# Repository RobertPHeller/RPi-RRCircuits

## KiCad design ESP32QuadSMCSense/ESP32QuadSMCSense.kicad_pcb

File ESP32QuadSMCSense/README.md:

# ESP32QuadSMCSense

ESP32 Quad Stall Motor w/ sense node.

* [Order this board from The Country Robot](https://www.thecountryrobot.com/product/quad-stall-motor-control-and-sense-board-for-esp32-bare-circuit-board-w-doc/)
* [Order this board from PCBWay](https://www.pcbway.com/project/shareproject/ESP32QuadSMCSense.html)

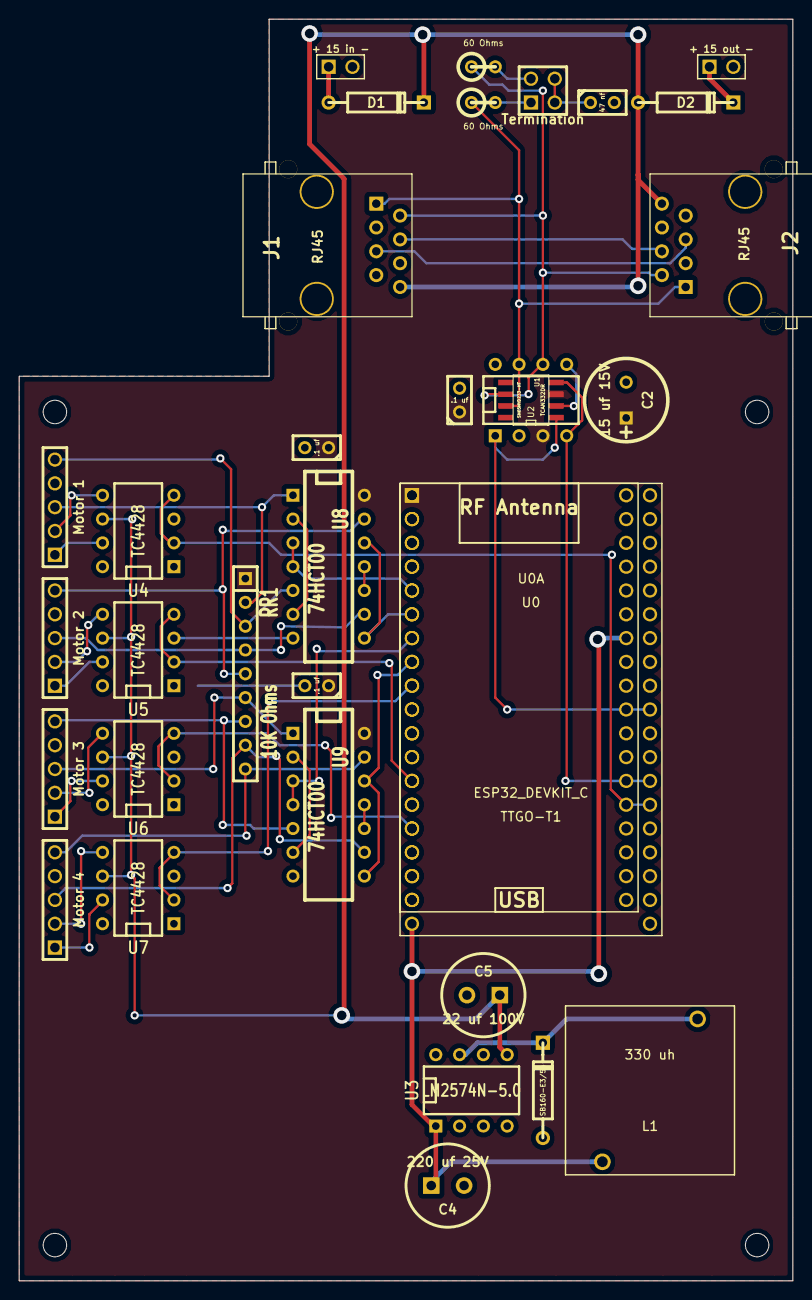
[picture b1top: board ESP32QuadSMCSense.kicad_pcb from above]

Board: 2 copper layers, 82.5 x 134.6 mm, 38 parts (0 on the bottom side), 44 nets.

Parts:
C1, C6, C7: .1 uf; C1
C2: 15 uf 15V; C1.5V8V
C3: 47 nf; C1
C4: 220 uf 25V; C1-3V8
C5: 22 uf 100V; C1-3V8
D1, D2: SB240E; DO-41
D3: SB160-E3/54; DO-41
J1, J2: RJ45; RJ45_8N-S
JP1: Termination; PIN_ARRAY_2X2
L1: 330 uh; PE-LowProfile
MH: MountingHole_2-5mm_RevA_Date21Jun2010
MH#2, MH#3, MH#4: MountingHole_2-5mm_RevA_Date21Jun2010
R1, R2: 60 Ohms; R1
RR1: 10K Ohms; SIL-9
T1: + 15 in -; ScrewTerm2.54-2
T2: + 15 out -; ScrewTerm2.54-2
T3: Motor 1; ScrewTerm_2.54-5
T4: Motor 2; ScrewTerm_2.54-5
T5: Motor 3; ScrewTerm_2.54-5
T6: Motor 4; ScrewTerm_2.54-5
U0: ESP32_DEVKIT_C; ESP32-Devkit-C
U0A: TTGO-T1; TIGO-T1
U1: TCAN332DR; SOIC-8_N
U2: SN65HVD233-HT; DIP-8__300
U3: LM2574N-5.0; DIP-8__300
U4, U5, U6, U7: TC4428; DIP-8__300
U8, U9: 74HCT00; DIP-14__300

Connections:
3V3: C1.1, C2.1, C6.1, C7.1, RR1.1, U0.1, U0A.1, U1.3, U2.3, U8.14, U9.14
+5V: C4.1, L1.1, U0.19, U0A.30, U3.1
+12V: C5.1, D1.2, D2.1, J1.8, J2.8, U3.5, U4.6, U5.6, U6.6, U7.6
/CAN Transceiver/CANH: J1.1, J2.1, R1.1, U1.7, U2.7
/CAN Transceiver/CANL: J1.2, J2.2, R2.1, U1.6, U2.6
/CAN Transceiver/CAN_RX: U0.26, U0A.24, U1.4, U2.4
/CAN Transceiver/CAN_TX: U0.29, U0A.27, U1.1, U2.1
/Motor1A: T3.1, U4.7
/Motor1B: T3.2, U4.5
/Motor2A: T4.1, U5.7
/Motor2B: T4.2, U5.5
/Motor3A: T5.1, U6.7
/Motor3B: T5.2, U6.5
/Motor4A: T6.1, U7.7
/Motor4B: T6.2, U7.5
/Motor 1: U0.25, U0A.23, U4.2, U4.4
/Motor 2: U0.13, U0A.13, U5.2, U5.4
/Motor 3: U0.15, U0A.15, U6.2, U6.4
/Motor 4: U0.9, U0A.9, U7.2, U7.4
/Points 1A: RR1.2, T3.3, U8.1
/Points 1B: RR1.3, T3.5, U8.5
/Points 2A: RR1.4, T4.3, U8.9
/Points 2B: RR1.5, T4.5, U8.13
/Points 3A: RR1.6, T5.3, U9.1
/Points 3B: RR1.7, T5.5, U9.5
/Points 4A: RR1.8, T6.3, U9.9
/Points 4B: RR1.9, T6.5, U9.13
/Sense 1: U0.5, U0A.5, U8.3, U8.4
/Sense 2: U0.6, U0A.6, U8.8, U8.12
/Sense 3: U0.7, U0A.7, U9.3, U9.4
/Sense 4: U0.8, U0A.8, U9.8, U9.12
GND: C1.2, C2.2, C3.2, C4.2, C5.2, C6.2, C7.2, D3.1, J1.3, J1.6, J1.7, J2.3, J2.6, J2.7, T1.2, T2.2, T3.4, T4.4, T5.4, T6.4, U0.14, U0.32, U0.38, U0A.14, U0A.36, U1.2, U2.2, U2.5, U2.8, U3.2, U3.3, U3.4, U4.3, U5.3, U6.3, U7.3, U8.7, U9.7
unnamed: U9.10, U9.11
unnamed: U8.10, U8.11
unnamed: U8.2, U8.6
unnamed: U9.2, U9.6
unnamed: J1.4, J2.4
unnamed: J1.5, J2.5
unnamed: D1.1, T1.1
unnamed: D2.2, T2.1
unnamed: JP1.2, R2.2
unnamed: JP1.1, R1.2
unnamed: C3.1, JP1.3, JP1.4
unnamed: D3.2, L1.2, U3.7

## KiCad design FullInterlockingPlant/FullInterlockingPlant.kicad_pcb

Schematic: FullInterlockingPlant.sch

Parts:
J1: RPI_GPIO
P1, P2, P3: CONN_5

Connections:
#4: J1.7, P1.2
#5: J1.29, P2.1
#6: J1.31, P2.2
#12: J1.32, P2.3
#13: J1.33, P2.4
#16: J1.36, P2.5
#19: J1.35, P3.1
#20: J1.38, P3.2
#21: J1.40, P3.3
#23: J1.16, P1.3
#24: J1.18, P1.4
#25: J1.22, P1.5
#26: J1.37, P3.4
+3.3V: J1.1, J1.17, P1.1; also elsewhere on the board
+5V: J1.2, J1.4; also elsewhere on the board
/StallMotors/M Select 2: J1.12; also elsewhere on the board
/StallMotors/MSelect 1: J1.11; also elsewhere on the board
/StallMotors/Point Sense 1: J1.13; also elsewhere on the board
/StallMotors/Point Sense 2: J1.15; also elsewhere on the board
GND: J1.6, J1.9, J1.14, J1.20, J1.25, J1.30, J1.34, J1.39, P3.5; also elsewhere on the board
SCL: J1.5; also elsewhere on the board
SDA: J1.3; also elsewhere on the board

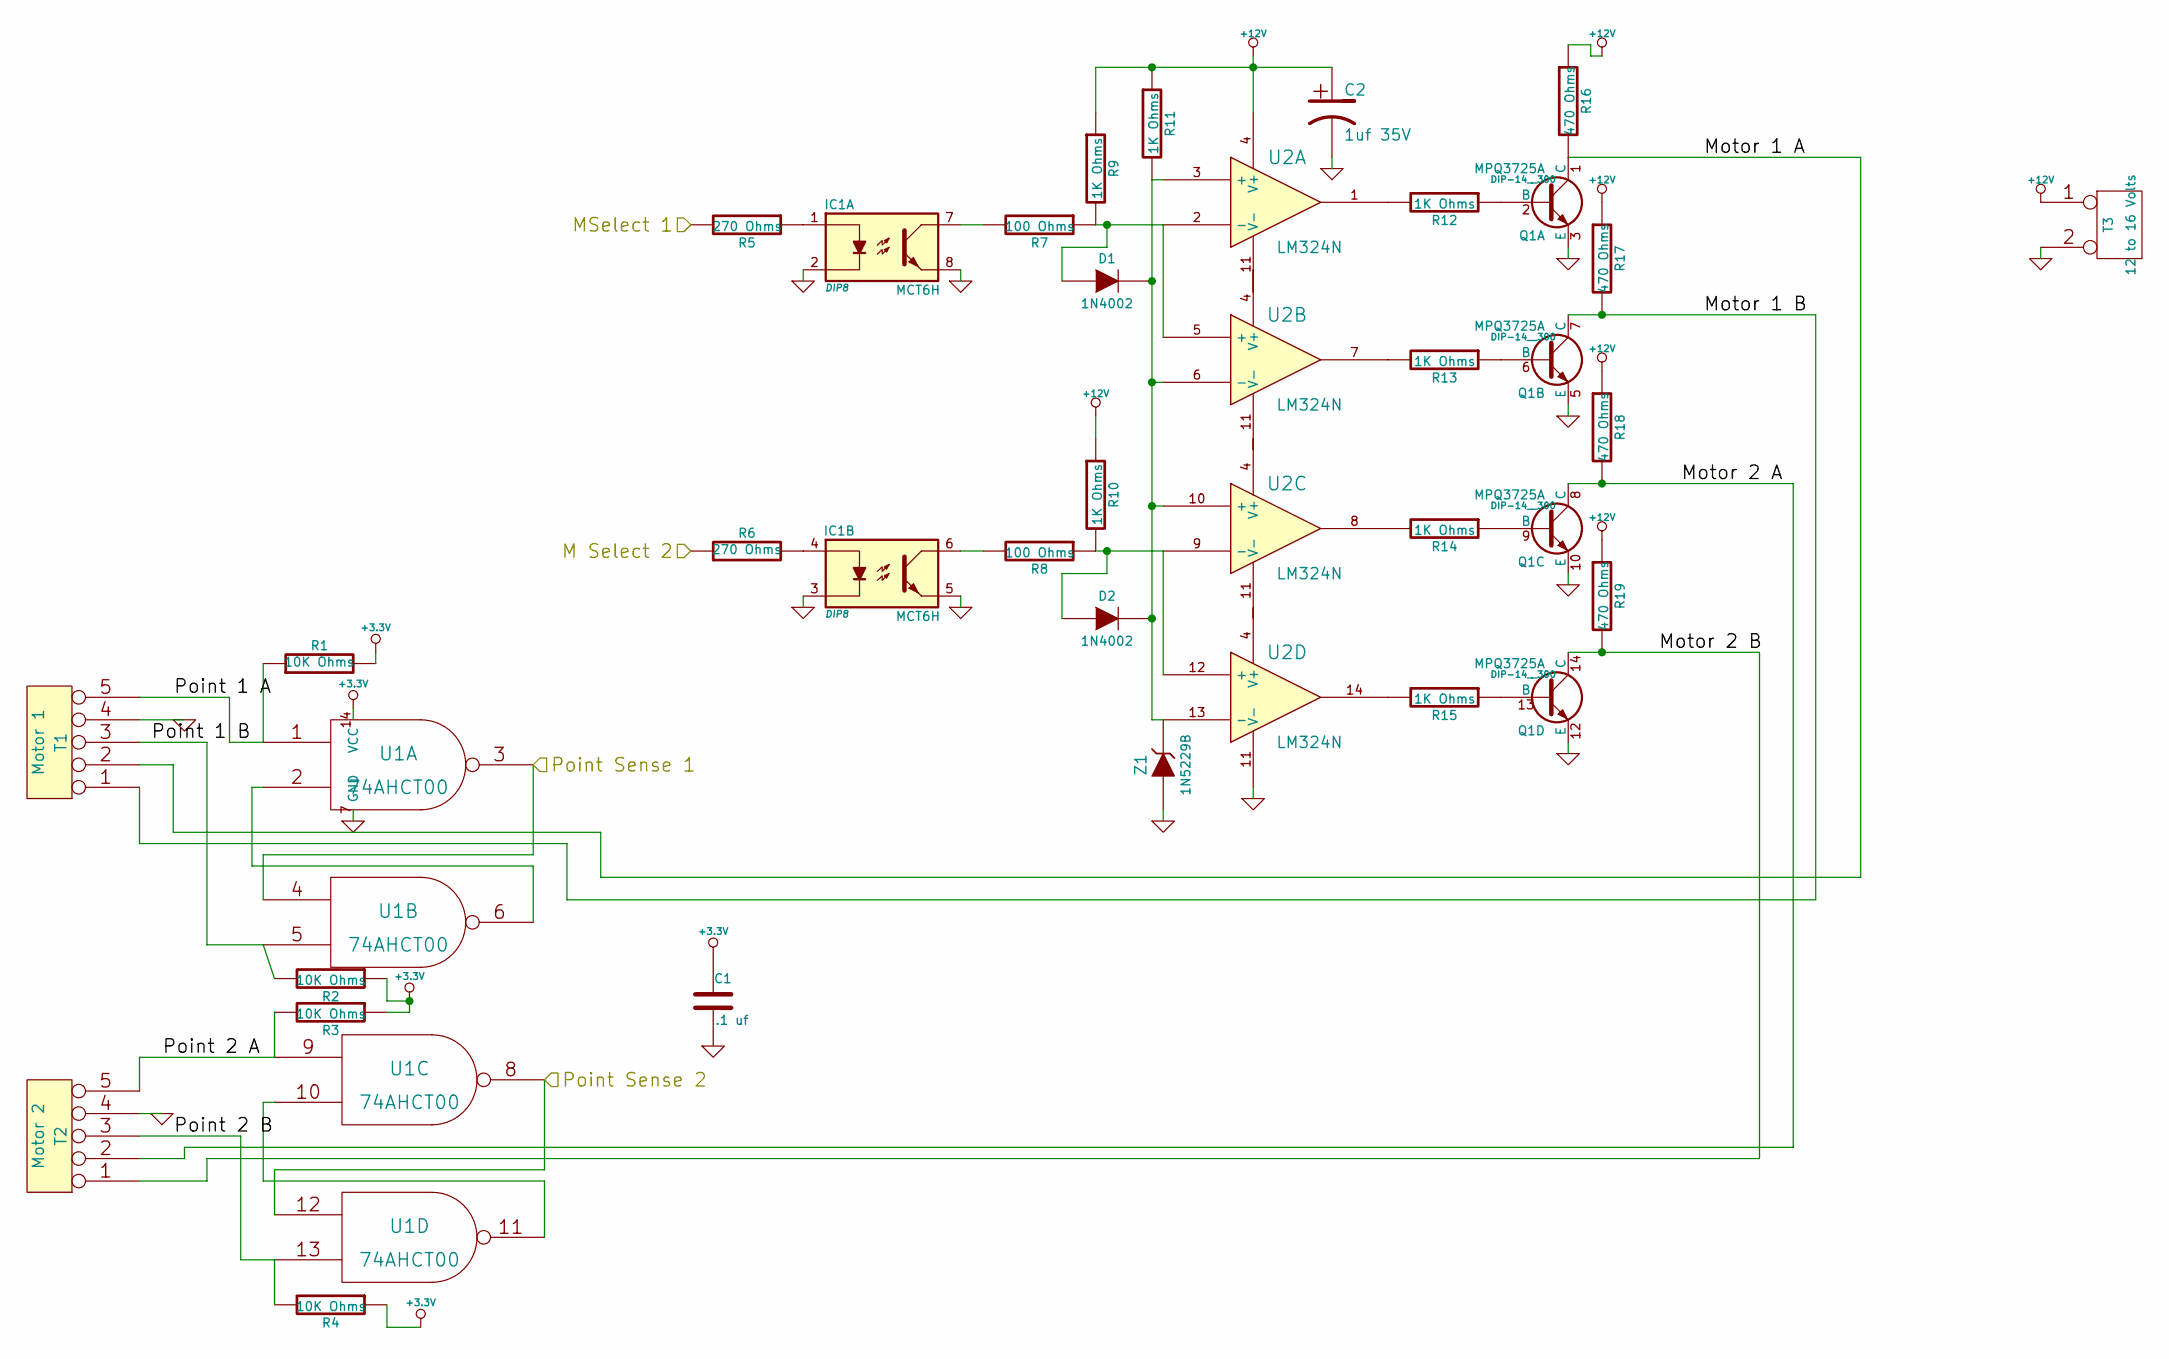
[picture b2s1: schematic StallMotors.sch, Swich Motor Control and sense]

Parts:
C1: .1 uf; Mouser part Number 21RZ310-RC
C2: 1uf 35V; Mouser Part Number 74-199D105X9035A1VE3
D1, D2: 1N4002; Mouser Part Number 833-1N4002-TP
IC1: MCT6H; DIP8; Mouser part Number 782-MCT6H
Q1: MPQ3725A; DIP-14__300; Mouser part Number 610-MPQ3725A
R1, R2, R3, R4: 10K Ohms; Mouser Part Number 603-CFR-25JR-5210K
R5, R6: 270 Ohms; Mouser Part Number 603-CFR-25JR-52-270R
R7, R8: 100 Ohms; Mouser Part Number 603-CFR-25JR-52100R
R9: 1K Ohms; Mouser part Number 279-2-1623927-3
R10, R11, R12, R13, R14, R15: 1K Ohms; Mouser Part Number 279-2-1623927-3
R16: 470 Ohms; Mouser part Number 279-CFR50J470R
R17, R18: 470 Ohms; Mouser Part Number 279-CFR50J470R
R19: 470 Ohms; Mousere Part Number 279-CFR50J470R
T1: Motor 1; Mouser Part Number 571-282834-5
T2: Motor 2; Mouser Part Number 571-282834-5
T3: 12 to 16 Volts; Mouser Partnumber 571-282834-2
U1: 74AHCT00; Mouser part Number 595-SN74AHC00N
U2: LM324N; Mouser part Number 512-LM324N
Z1: 1N5229B; Mouser Part Number 512-1N5229BTR

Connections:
+3.3V: C1.1, R1.2, R2.1, R3.1, R4.1, U1.14 (VCC); also elsewhere on the board
+12V: C2.1, R9.1, R10.1, R11.1, R16.1, R17.1, R18.1, R19.1, T3.1, U2.4 (V+)
/StallMotors/M Select 2: R6.1; also elsewhere on the board
/StallMotors/MSelect 1: R5.2; also elsewhere on the board
/StallMotors/Motor 1 A: Q1.1 (C), R16.2, T1.2
/StallMotors/Motor 1 B: Q1.7 (C), R17.2, T1.1
/StallMotors/Motor 2 A: Q1.8 (C), R18.2, T2.2
/StallMotors/Motor 2 B: Q1.14 (C), R19.2, T2.1
/StallMotors/Point 1 A: R1.1, T1.5, U1.1
/StallMotors/Point 1 B: R2.2, T1.3, U1.5
/StallMotors/Point 2 A: R3.2, T2.5, U1.9
/StallMotors/Point 2 B: R4.2, T2.3, U1.13
/StallMotors/Point Sense 1: U1.3, U1.4; also elsewhere on the board
/StallMotors/Point Sense 2: U1.8, U1.12; also elsewhere on the board
GND: C1.2, C2.2, IC1.2, IC1.3, IC1.5, IC1.8, Q1.3 (E), Q1.5 (E), Q1.10 (E), Q1.12 (E), T1.4, T2.4, T3.2 (PM), U1.7 (GND), U2.11 (V-), Z1.1 (A); also elsewhere on the board
unnamed: Q1.6 (B), R13.1
unnamed: Q1.9 (B), R14.1
unnamed: Q1.13 (B), R15.1
unnamed: Q1.2 (B), R12.1
unnamed: R12.2, U2.1
unnamed: R13.2, U2.7
unnamed: R14.2, U2.8
unnamed: R15.2, U2.14
unnamed: IC1.6, R8.2
unnamed: D2.1 (A), R8.1, R10.2, U2.9 (-), U2.12 (+)
unnamed: IC1.4, R6.2
unnamed: IC1.1, R5.1
unnamed: U1.2, U1.6
unnamed: IC1.7, R7.2
unnamed: U1.10, U1.11
unnamed: D1.2 (K), D2.2 (K), R11.2, U2.3 (+), U2.6 (-), U2.10 (+), U2.13 (-), Z1.2 (K)
unnamed: D1.1 (A), R7.1, R9.2, U2.2 (-), U2.5 (+)

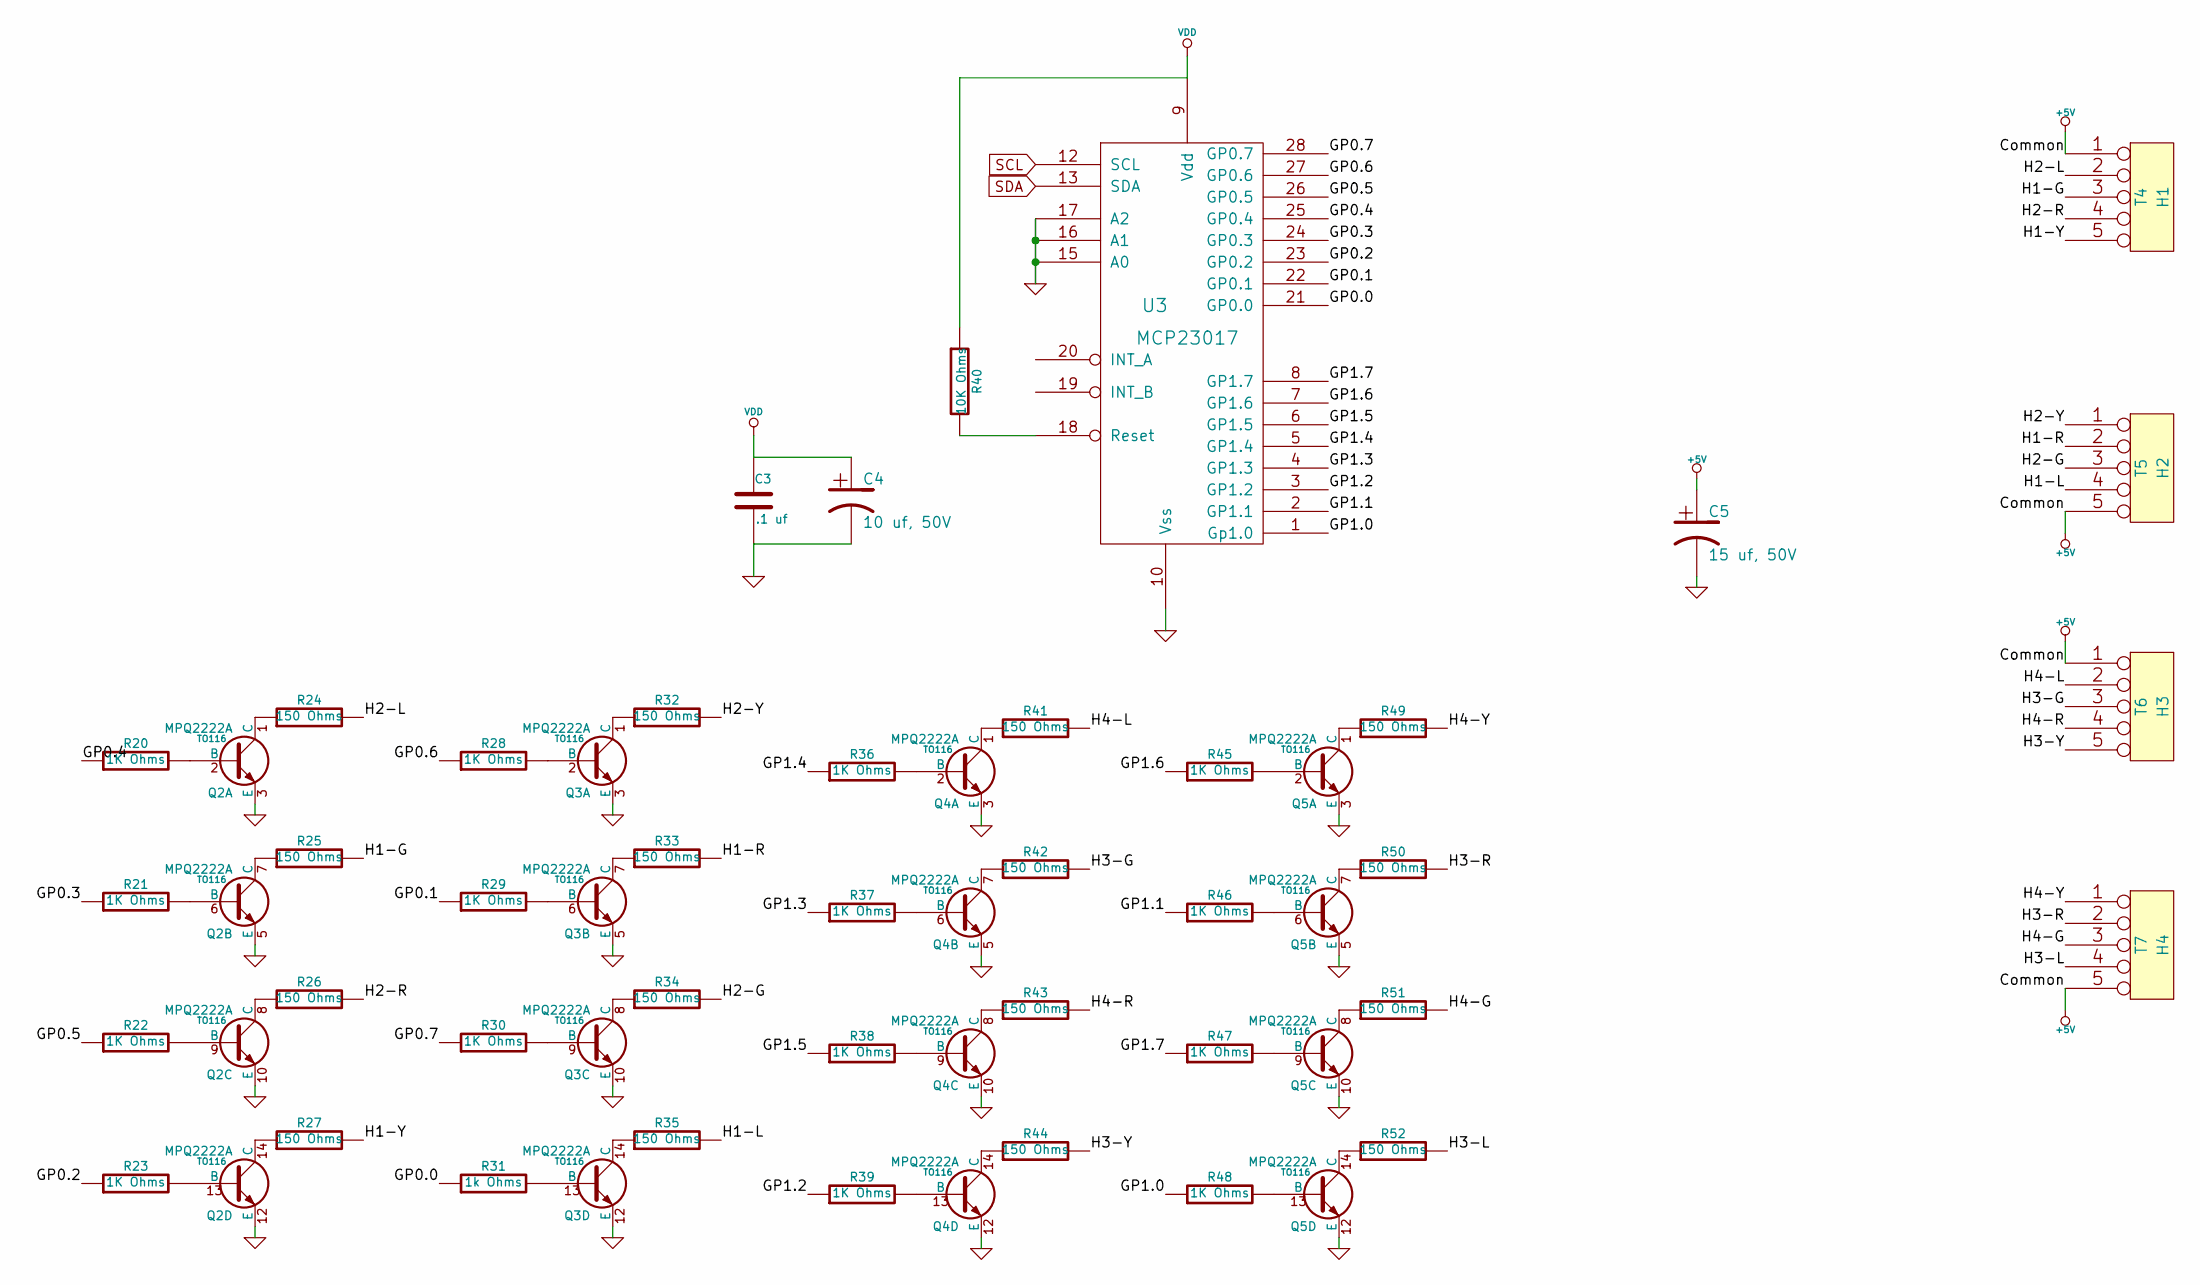
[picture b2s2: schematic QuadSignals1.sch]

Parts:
C3: .1 uf
C4: 10 uf, 50V
C5: 15 uf, 50V
Q2, Q3, Q4, Q5: MPQ2222A; TO116
R20, R21, R22, R23, R28, R29, R30, R36, R37, R38, R39, R45, R46, R47, R48: 1K Ohms
R24, R25, R26, R27, R32, R33, R34, R35, R41, R42, R43, R44, R49, R50, R51, R52: 150 Ohms
R31: 1k Ohms
R40: 10K Ohms
T4: H1
T5: H2
T6: H3
T7: H4
U3: MCP23017

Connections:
+3.3V: C3.1, C4.1, R40.1, U3.9 (Vdd); also elsewhere on the board
+5V: C5.1, T4.1, T5.5, T6.1, T7.5; also elsewhere on the board
/Quad Signals 1/GP0.0: R31.1, U3.21 (GP0.0)
/Quad Signals 1/GP0.1: R29.1, U3.22 (GP0.1)
/Quad Signals 1/GP0.2: R23.1, U3.23 (GP0.2)
/Quad Signals 1/GP0.3: R21.1, U3.24 (GP0.3)
/Quad Signals 1/GP0.4: R20.1, U3.25 (GP0.4)
/Quad Signals 1/GP0.5: R22.1, U3.26 (GP0.5)
/Quad Signals 1/GP0.6: R28.1, U3.27 (GP0.6)
/Quad Signals 1/GP0.7: R30.1, U3.28 (GP0.7)
/Quad Signals 1/GP1.0: R48.1, U3.1 (Gp1.0)
/Quad Signals 1/GP1.1: R46.1, U3.2 (GP1.1)
/Quad Signals 1/GP1.2: R39.1, U3.3 (GP1.2)
/Quad Signals 1/GP1.3: R37.1, U3.4 (GP1.3)
/Quad Signals 1/GP1.4: R36.1, U3.5 (GP1.4)
/Quad Signals 1/GP1.5: R38.1, U3.6 (GP1.5)
/Quad Signals 1/GP1.6: R45.1, U3.7 (GP1.6)
/Quad Signals 1/GP1.7: R47.1, U3.8 (GP1.7)
/Quad Signals 1/H1-G: R25.2, T4.3
/Quad Signals 1/H1-L: R35.2, T5.4
/Quad Signals 1/H1-R: R33.2, T5.2
/Quad Signals 1/H1-Y: R27.2, T4.5
/Quad Signals 1/H2-G: R34.2, T5.3
/Quad Signals 1/H2-L: R24.2, T4.2
/Quad Signals 1/H2-R: R26.2, T4.4
/Quad Signals 1/H2-Y: R32.2, T5.1
/Quad Signals 1/H3-G: R42.2, T6.3
/Quad Signals 1/H3-L: R52.2, T7.4
/Quad Signals 1/H3-R: R50.2, T7.2
/Quad Signals 1/H3-Y: R44.2, T6.5
/Quad Signals 1/H4-G: R51.2, T7.3
/Quad Signals 1/H4-L: R41.2, T6.2
/Quad Signals 1/H4-R: R43.2, T6.4
/Quad Signals 1/H4-Y: R49.2, T7.1
GND: C3.2, C4.2, C5.2, Q2.3 (E), Q2.5 (E), Q2.10 (E), Q2.12 (E), Q3.3 (E), Q3.5 (E), Q3.10 (E), Q3.12 (E), Q4.3 (E), Q4.5 (E), Q4.10 (E), Q4.12 (E), Q5.3 (E), Q5.5 (E), Q5.10 (E), Q5.12 (E), U3.10 (Vss), U3.15 (A0), U3.16 (A1), U3.17 (A2); also elsewhere on the board
unnamed: Q5.14 (C), R52.1
unnamed: Q5.13 (B), R48.2
unnamed: Q5.8 (C), R51.1
unnamed: Q5.9 (B), R47.2
unnamed: R40.2, U3.18 (Reset)
unnamed: Q2.13 (B), R23.2
unnamed: Q2.14 (C), R27.1
unnamed: Q2.8 (C), R26.1
unnamed: Q2.9 (B), R22.2
unnamed: Q2.7 (C), R25.1
unnamed: Q3.6 (B), R29.2
unnamed: Q3.7 (C), R33.1
unnamed: Q3.1 (C), R32.1
unnamed: Q3.2 (B), R28.2
unnamed: Q2.6 (B), R21.2
unnamed: Q2.1 (C), R24.1
unnamed: Q2.2 (B), R20.2
unnamed: Q4.14 (C), R44.1
unnamed: Q4.13 (B), R39.2
unnamed: Q4.8 (C), R43.1
unnamed: Q4.9 (B), R38.2
unnamed: Q5.7 (C), R50.1
unnamed: Q5.6 (B), R46.2
unnamed: Q5.1 (C), R49.1
unnamed: Q5.2 (B), R45.2
unnamed: Q3.13 (B), R31.2
unnamed: Q3.14 (C), R35.1
unnamed: Q3.8 (C), R34.1
unnamed: Q3.9 (B), R30.2
unnamed: Q4.7 (C), R42.1
unnamed: Q4.6 (B), R37.2
unnamed: Q4.1 (C), R41.1
unnamed: Q4.2 (B), R36.2
SCL: U3.12 (SCL); also elsewhere on the board
SDA: U3.13 (SDA); also elsewhere on the board

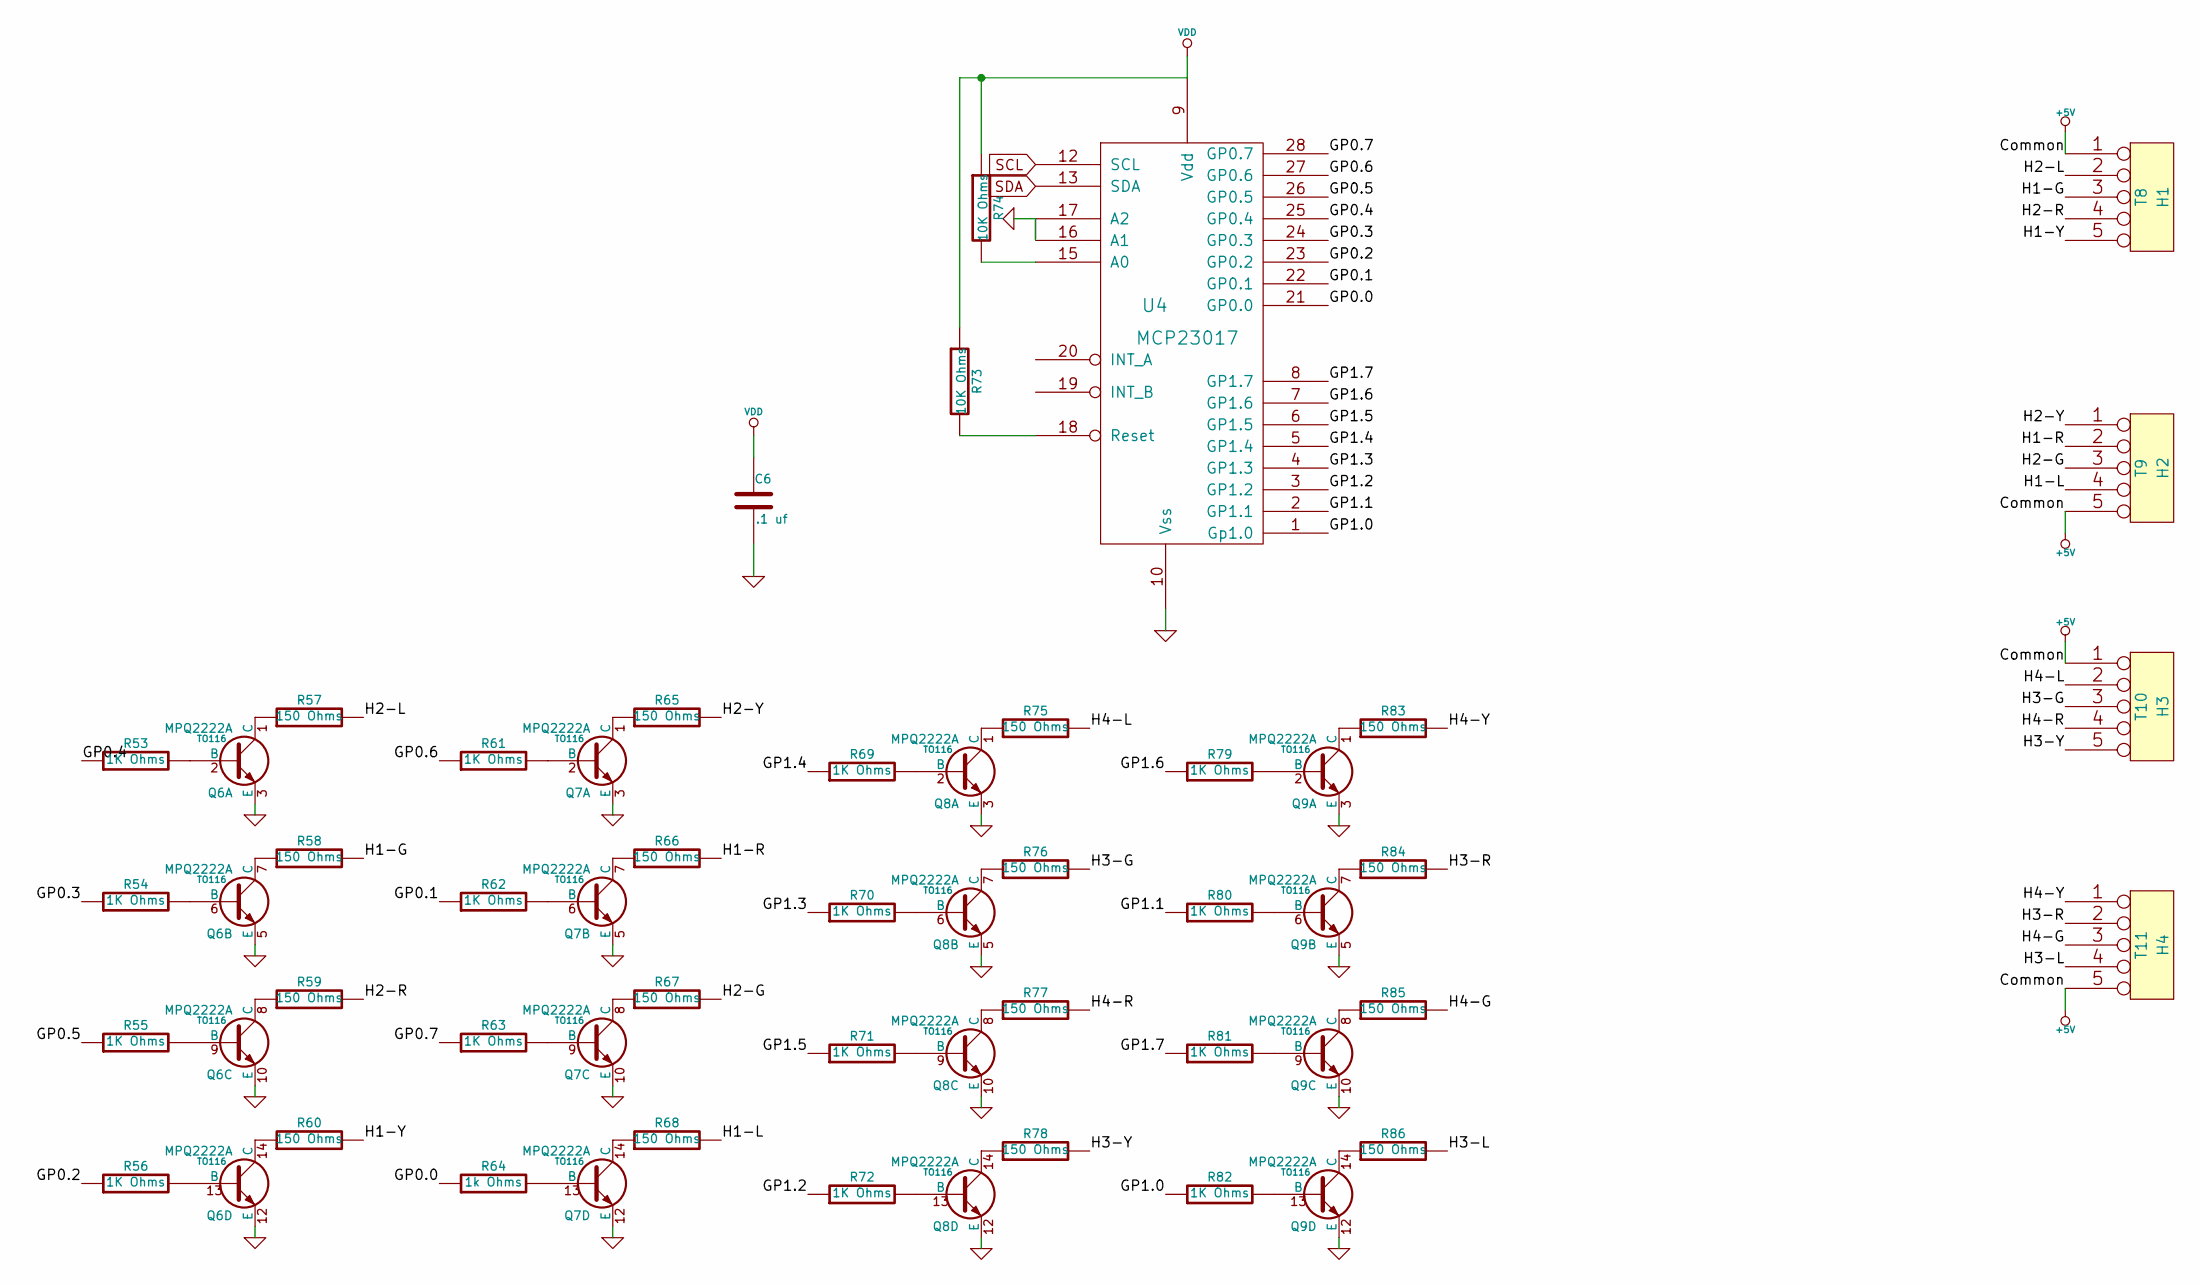
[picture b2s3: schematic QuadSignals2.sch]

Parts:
C6: .1 uf
Q6, Q7, Q8, Q9: MPQ2222A; TO116
R53, R54, R55, R56, R61, R62, R63, R69, R70, R71, R72, R79, R80, R81, R82: 1K Ohms
R57, R58, R59, R60, R65, R66, R67, R68, R75, R76, R77, R78, R83, R84, R85, R86: 150 Ohms
R64: 1k Ohms
R73, R74: 10K Ohms
T8: H1
T9: H2
T10: H3
T11: H4
U4: MCP23017

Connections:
+3.3V: C6.1, R73.1, R74.1, U4.9 (Vdd); also elsewhere on the board
+5V: T8.1, T9.5, T10.1, T11.5; also elsewhere on the board
/Quad Signals 2/GP0.0: R64.1, U4.21 (GP0.0)
/Quad Signals 2/GP0.1: R62.1, U4.22 (GP0.1)
/Quad Signals 2/GP0.2: R56.1, U4.23 (GP0.2)
/Quad Signals 2/GP0.3: R54.1, U4.24 (GP0.3)
/Quad Signals 2/GP0.4: R53.1, U4.25 (GP0.4)
/Quad Signals 2/GP0.5: R55.1, U4.26 (GP0.5)
/Quad Signals 2/GP0.6: R61.1, U4.27 (GP0.6)
/Quad Signals 2/GP0.7: R63.1, U4.28 (GP0.7)
/Quad Signals 2/GP1.0: R82.1, U4.1 (Gp1.0)
/Quad Signals 2/GP1.1: R80.1, U4.2 (GP1.1)
/Quad Signals 2/GP1.2: R72.1, U4.3 (GP1.2)
/Quad Signals 2/GP1.3: R70.1, U4.4 (GP1.3)
/Quad Signals 2/GP1.4: R69.1, U4.5 (GP1.4)
/Quad Signals 2/GP1.5: R71.1, U4.6 (GP1.5)
/Quad Signals 2/GP1.6: R79.1, U4.7 (GP1.6)
/Quad Signals 2/GP1.7: R81.1, U4.8 (GP1.7)
/Quad Signals 2/H1-G: R58.2, T8.3
/Quad Signals 2/H1-L: R68.2, T9.4
/Quad Signals 2/H1-R: R66.2, T9.2
/Quad Signals 2/H1-Y: R60.2, T8.5
/Quad Signals 2/H2-G: R67.2, T9.3
/Quad Signals 2/H2-L: R57.2, T8.2
/Quad Signals 2/H2-R: R59.2, T8.4
/Quad Signals 2/H2-Y: R65.2, T9.1
/Quad Signals 2/H3-G: R76.2, T10.3
/Quad Signals 2/H3-L: R86.2, T11.4
/Quad Signals 2/H3-R: R84.2, T11.2
/Quad Signals 2/H3-Y: R78.2, T10.5
/Quad Signals 2/H4-G: R85.2, T11.3
/Quad Signals 2/H4-L: R75.2, T10.2
/Quad Signals 2/H4-R: R77.2, T10.4
/Quad Signals 2/H4-Y: R83.2, T11.1
GND: C6.2, Q6.3 (E), Q6.5 (E), Q6.10 (E), Q6.12 (E), Q7.3 (E), Q7.5 (E), Q7.10 (E), Q7.12 (E), Q8.3 (E), Q8.5 (E), Q8.10 (E), Q8.12 (E), Q9.3 (E), Q9.5 (E), Q9.10 (E), Q9.12 (E), U4.10 (Vss), U4.16 (A1), U4.17 (A2); also elsewhere on the board
unnamed: Q9.13 (B), R82.2
unnamed: Q9.8 (C), R85.1
unnamed: Q9.9 (B), R81.2
unnamed: Q9.7 (C), R84.1
unnamed: Q9.6 (B), R80.2
unnamed: Q9.14 (C), R86.1
unnamed: R74.2, U4.15 (A0)
unnamed: R73.2, U4.18 (Reset)
unnamed: Q6.14 (C), R60.1
unnamed: Q6.13 (B), R56.2
unnamed: Q6.8 (C), R59.1
unnamed: Q6.9 (B), R55.2
unnamed: Q6.7 (C), R58.1
unnamed: Q6.6 (B), R54.2
unnamed: Q7.7 (C), R66.1
unnamed: Q7.6 (B), R62.2
unnamed: Q7.1 (C), R65.1
unnamed: Q7.2 (B), R61.2
unnamed: Q6.1 (C), R57.1
unnamed: Q6.2 (B), R53.2
unnamed: Q8.13 (B), R72.2
unnamed: Q8.8 (C), R77.1
unnamed: Q8.9 (B), R71.2
unnamed: Q8.7 (C), R76.1
unnamed: Q8.6 (B), R70.2
unnamed: Q9.1 (C), R83.1
unnamed: Q9.2 (B), R79.2
unnamed: Q8.14 (C), R78.1
unnamed: Q7.14 (C), R68.1
unnamed: Q7.13 (B), R64.2
unnamed: Q7.8 (C), R67.1
unnamed: Q7.9 (B), R63.2
unnamed: Q8.1 (C), R75.1
unnamed: Q8.2 (B), R69.2
SCL: U4.12 (SCL); also elsewhere on the board
SDA: U4.13 (SDA); also elsewhere on the board

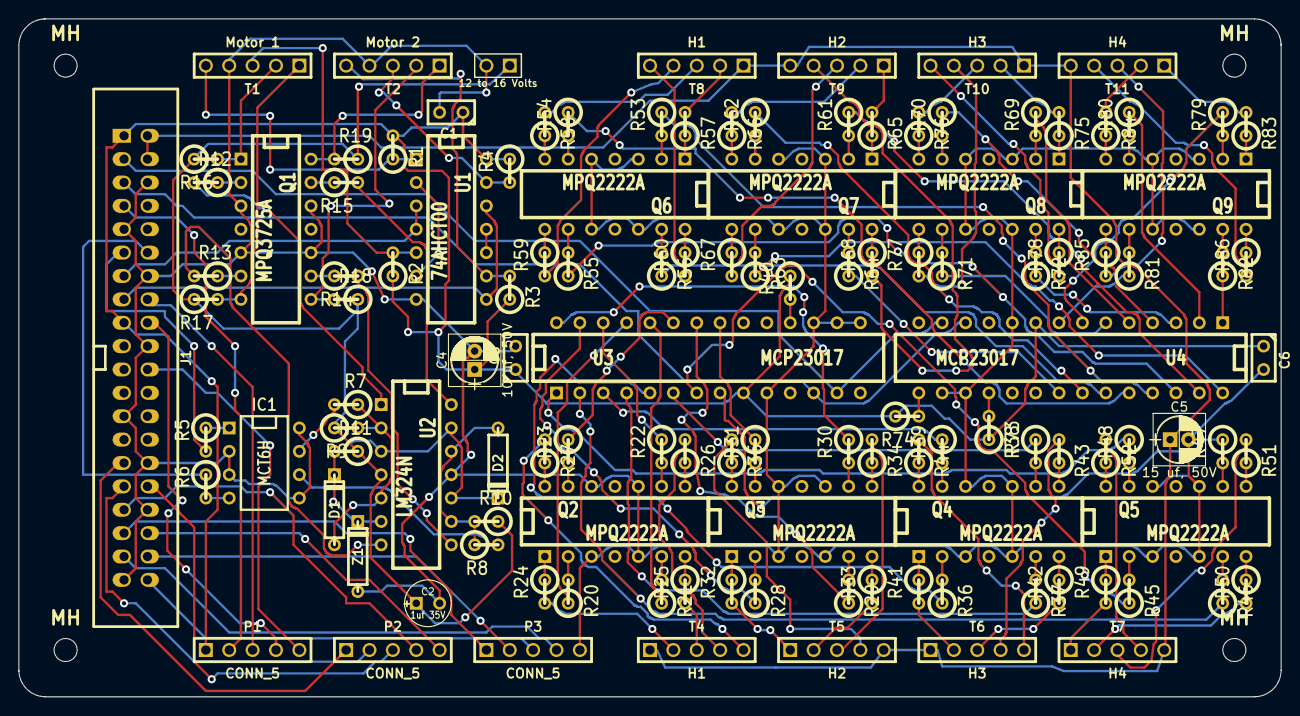
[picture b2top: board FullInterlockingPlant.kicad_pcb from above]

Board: 2 copper layers, 137.2 x 73.7 mm, 128 parts (0 on the bottom side), 179 nets.

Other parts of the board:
MH: MountingHole_2-5mm_RevA_Date21Jun2010
MH#2, MH#3, MH#4: MountingHole_2-5mm_RevA_Date21Jun2010

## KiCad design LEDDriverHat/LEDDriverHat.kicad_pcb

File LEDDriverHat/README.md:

# LEDDriverHat

Eight LED drivers.  Jumpers to select GPIO pins.

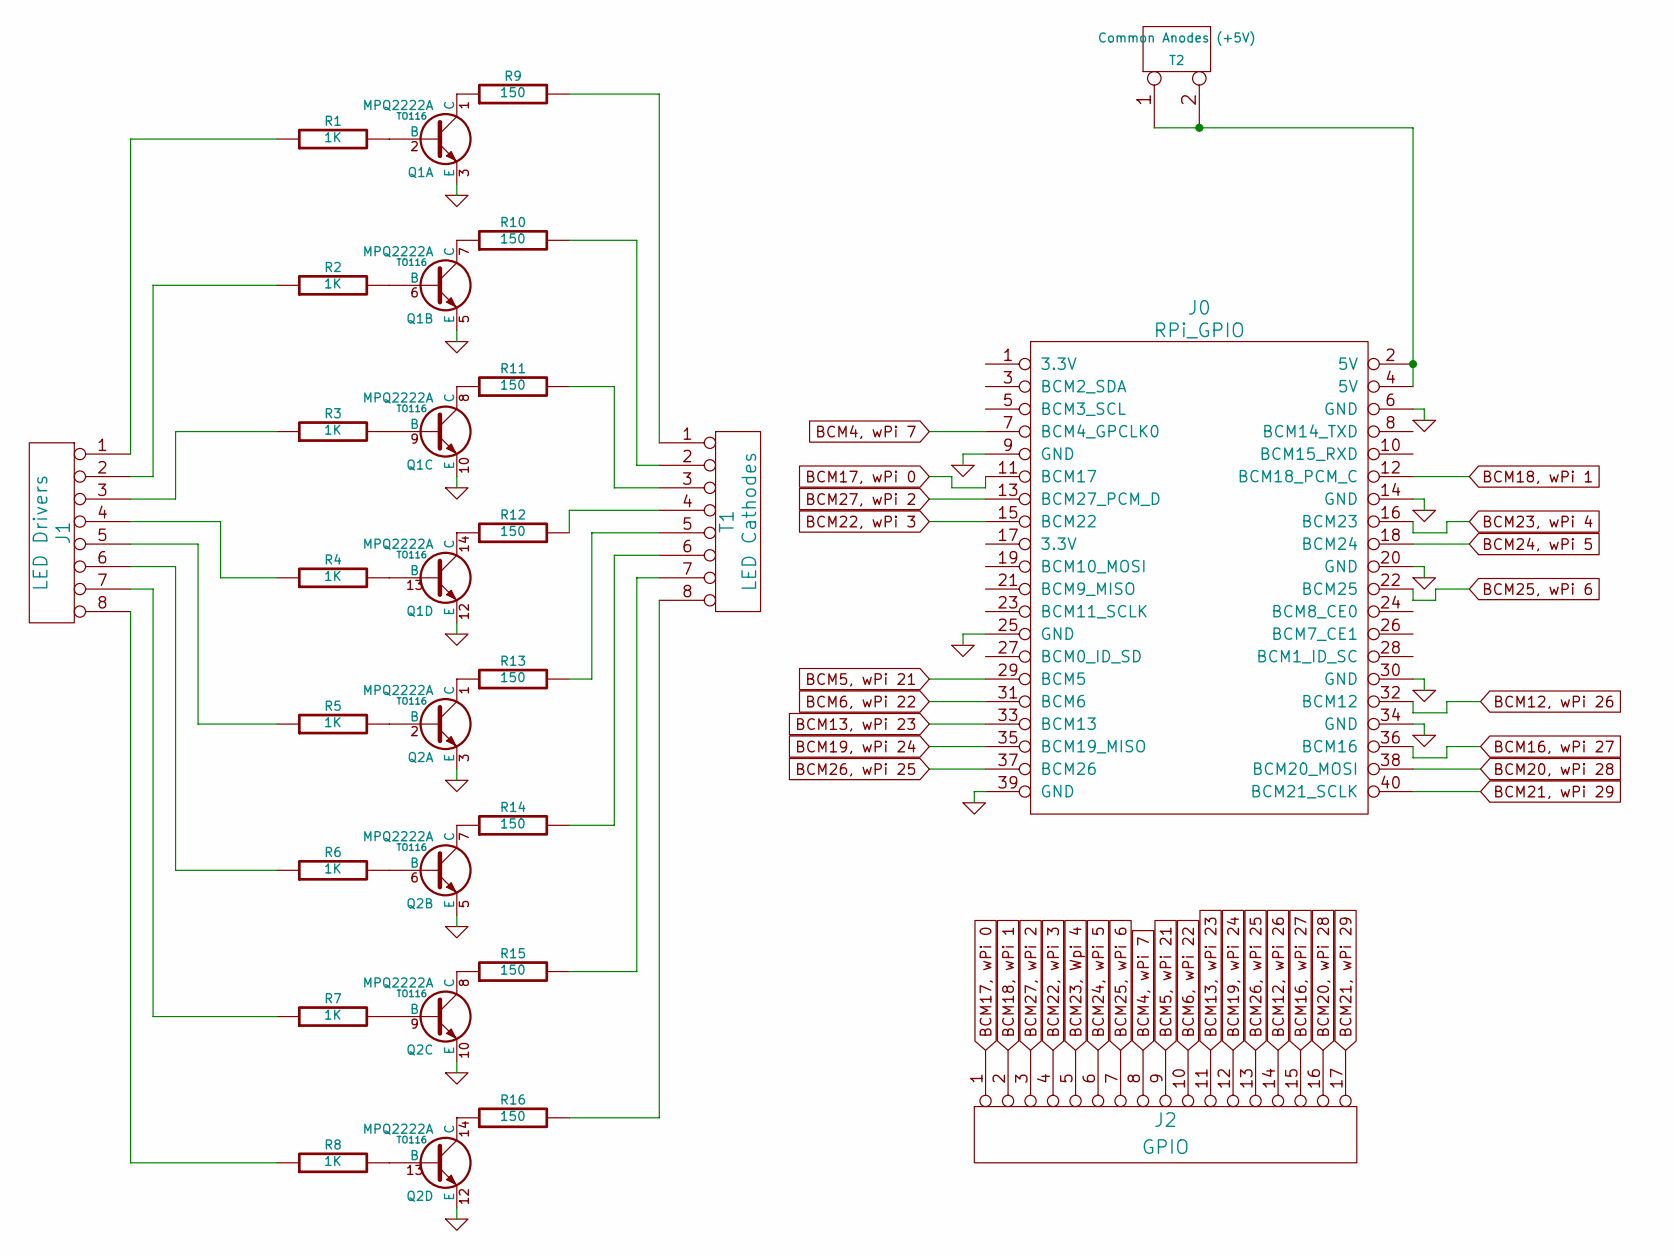
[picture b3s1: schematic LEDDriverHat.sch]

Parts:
J0: RPi_GPIO; Pin_Header_Straight_2x20; Mouser Part Number 855-M20-6102045
J1: LED Drivers; Mouser Part Number 992-8FX1L-254MM
J2: GPIO; Mouser Part Number 517-929974-01-17-RK
Q1, Q2: MPQ2222A; TO116; Mouser Part Number 610-MPQ2222A
R1, R2, R3, R4, R5, R6, R7, R8: 1K; Mouser Part Number 660-MS1/4DCT52R1001
R9, R10, R11, R12, R13, R14, R15, R16: 150; Mouser Part Number 603-MFR-25FBF52-150R
T1: LED Cathodes; Mouser Part Number 651-1725711
T2: Common Anodes (+5V); Mouser Part Number 571-282834-2

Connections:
BCM4, wPi 7: J0.7 (BCM4_GPCLK0), J2.8
BCM5, wPi 21: J0.29 (BCM5), J2.9
BCM6, wPi 22: J0.31 (BCM6), J2.10
BCM12, wPi 26: J0.32 (BCM12), J2.14
BCM13, wPi 23: J0.33 (BCM13), J2.11
BCM16, wPi 27: J0.36 (BCM16), J2.15
BCM17, wPi 0: J0.11 (BCM17), J2.1
BCM18, wPi 1: J0.12 (BCM18_PCM_C), J2.2
BCM19, wPi 24: J0.35 (BCM19_MISO), J2.12
BCM20, wPi 28: J0.38 (BCM20_MOSI), J2.16
BCM21, wPi 29: J0.40 (BCM21_SCLK), J2.17
BCM22, wPi 3: J0.15 (BCM22), J2.4
BCM23, Wpi 4: J0.16 (BCM23), J2.5
BCM24, wPi 5: J0.18 (BCM24), J2.6
BCM25, wPi 6: J0.22 (BCM25), J2.7
BCM26, wPi 25: J0.37 (BCM26), J2.13
BCM27, wPi 2: J0.13 (BCM27_PCM_D), J2.3
GND: J0.6 (GND), J0.9 (GND), J0.14 (GND), J0.20 (GND), J0.25 (GND), J0.30 (GND), J0.34 (GND), J0.39 (GND), Q1.3 (E), Q1.5 (E), Q1.10 (E), Q1.12 (E), Q2.3 (E), Q2.5 (E), Q2.10 (E), Q2.12 (E)
unnamed: R11.2, T1.3
unnamed: R10.2, T1.2
unnamed: R9.2, T1.1
unnamed: R12.2, T1.4
unnamed: J1.5, R5.1
unnamed: J1.4, R4.1
unnamed: J1.3, R3.1
unnamed: J1.2, R2.1
unnamed: J1.1, R1.1
unnamed: R13.2, T1.5
unnamed: R14.2, T1.6
unnamed: R15.2, T1.7
unnamed: R16.2, T1.8
unnamed: J1.8, R8.1
unnamed: J1.7, R7.1
unnamed: J1.6, R6.1
unnamed: Q1.7 (C), R10.1
unnamed: Q1.6 (B), R2.2
unnamed: Q1.1 (C), R9.1
unnamed: Q1.2 (B), R1.2
unnamed: Q1.14 (C), R12.1
unnamed: Q1.13 (B), R4.2
unnamed: Q1.8 (C), R11.1
unnamed: Q1.9 (B), R3.2
unnamed: J0.2 (5V), J0.4 (5V), T2.1, T2.2 (PM)
unnamed: Q2.7 (C), R14.1
unnamed: Q2.6 (B), R6.2
unnamed: Q2.1 (C), R13.1
unnamed: Q2.2 (B), R5.2
unnamed: Q2.14 (C), R16.1
unnamed: Q2.13 (B), R8.2
unnamed: Q2.8 (C), R15.1
unnamed: Q2.9 (B), R7.2

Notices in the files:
LEDDriverHat/LEDDriverHat.kicad_pcb:
(c) Copyright 2017 Deepwoods Software
LPC1754-MultiIOBoard/LPC1754-MultiIOBoard.kicad_pcb:
(C) 2022 Robert Heller D/B/A Deepwoods Software
